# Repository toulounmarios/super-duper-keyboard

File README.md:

helloooooooooooooooooooooo, if you are reading this then you are at the readme section of this repo, so pretty am i right? i know, i know.
im building this project so that i can FINALLY step away from using an old 25 euro gaming keyboard with blue switches ( VERY LOUD ) and make
a compact and aesthetic split keyboad that looks and sounds nice, while also not waking up my entire family at 3am while playing ultrakill or Apex Legends ( both goated btw).
anyways, for anyone who is suprisingly interested in my project here are the key components of the build as well as my key take aways from my first project and some inspo for this.

  first of all, the microcontrollers im using are a pair of seeed xiao nRF52840s, the normal ones will do just fine.
    the pcb was designed on kicad with the libraries from the hackclub stasis event starter project (the split keyboard one) and is manufactured via jlcpcb
   my switches are the kailh choc v2 deep sea silent whale brown switches, due to their tactile yet silent profile.
   for the batteries i havent decided on a li-po battery size for now
  both the case and keycaps ill design after i get the pcb in hand for refernce and ideas 

Now, as for my mistakes, there are afew:

 &emsp; 1) its best to split the work into chunks and finish them consistently. you dont have to do evrything immidiatly, 
    but try to do related tasks back to back to avoid forgetting where you are at in the build process

 &emsp; 2) try to simplify your models in the pcb editor as much as possible. this is because services like jlcpcb change the shipping 
    and manufacturing costs drastically depending on the size of the pcb, but also stuff like the number of layers on your pcb or the pating and stuff

 &emsp; 3) thats it for now

my key inspo for this project was the corne layout for split keyboards and the typeractive corn pcb aluminum case for the pcb and case design

here are the schematics: [schematic](KiCAD_files/keyboard_1.kicad_sch)

here is the pcb design for you to put it into jlcpcb: [pcb](KiCAD_files/keyboard_1.kicad_pcb)

here are pics of the bottom and top plates of the case (all files are in the 3D models folder): 

also here are some sweet renders! 

here is the BOM :

| Name                                           | Purpose                                        | Qty | Total (USD) | Link                                                                                                                                                                                                                                                                                                                                                                                                                                                                                                                                                                                                                                                                                                                                                                                                                                                                                                                                                                                                                                                          | Distributor  |   |
|------------------------------------------------|------------------------------------------------|-----|-------------|---------------------------------------------------------------------------------------------------------------------------------------------------------------------------------------------------------------------------------------------------------------------------------------------------------------------------------------------------------------------------------------------------------------------------------------------------------------------------------------------------------------------------------------------------------------------------------------------------------------------------------------------------------------------------------------------------------------------------------------------------------------------------------------------------------------------------------------------------------------------------------------------------------------------------------------------------------------------------------------------------------------------------------------------------------------|--------------|---|
|                                                |                                                |     |             |                                                                                                                                                                                                                                                                                                                                                                                                                                                                                                                                                                                                                                                                                                                                                                                                                                                                                                                                                                                                                                                               |              |   |
|                                                |                                                |     |             |                                                                                                                                                                                                                                                                                                                                                                                                                                                                                                                                                                                                                                                                                                                                                                                                                                                                                                                                                                                                                                                               |              |   |
| Seeed Studio XIAO nRF52840 (XIAO BLE)          | they are the microcontrollers                  | 2   | $19.80      | <a href=https://www.seeedstudio.com/Seeed-XIAO-BLE-nRF52840-p-5201.html>link</a>                                                                                                                                                                                                                                                                                                                                                                                                                                                                                                                                                                                                                                                                                                                                                                                                                                                                                                                                                                              | seeed studio |   |
|                                                |                                                |     |             |                                                                                                                                                                                                                                                                                                                                                                                                                                                                                                                                                                                                                                                                                                                                                                                                                                                                                                                                                                                                                                                               |              |   |
|                                                |                                                |     |             |                                                                                                                                                                                                                                                                                                                                                                                                                                                                                                                                                                                                                                                                                                                                                                                                                                                                                                                                                                                                                                                               |              |   |
| 0805 806k resistors                            | for part of vbat                               | 100 | $1.68       | <a href=https://www.aliexpress.com/item/1005005184230104.html?spm=a2g0o.productlist.main.1.6249IJXxIJXxPH&algo_pvid=938eadd9-71ba-4352-88da-76219ebfed72&algo_exp_id=938eadd9-71ba-4352-88da-76219ebfed72-0&pdp_ext_f=%7B%22order%22%3A%2216%22%2C%22eval%22%3A%221%22%2C%22fromPage%22%3A%22search%22%7D&pdp_npi=6%40dis%21EUR%212.25%210.86%21%21%2117.66%216.76%21%402103894417762777976955069ec2d7%2112000032017018112%21sea%21GR%216010249690%21ABX%211%210%21n_tag%3A-29910%3Bd%3A8b9bcfc7%3Bm03_new_user%3A-29895%3BpisId%3A5000000203610259&curPageLogUid=4cgpcI0GnRlD&utparam-url=scene%3Asearch%7Cquery_from%3A%7Cx_object_id%3A1005005184230104%7C_p_origin_prod%3A>link</a>                                                                                                                                                                                                                                                                                                                                                                       | aliexpress   |   |
|                                                |                                                |     |             |                                                                                                                                                                                                                                                                                                                                                                                                                                                                                                                                                                                                                                                                                                                                                                                                                                                                                                                                                                                                                                                               |              |   |
|                                                |                                                |     |             |                                                                                                                                                                                                                                                                                                                                                                                                                                                                                                                                                                                                                                                                                                                                                                                                                                                                                                                                                                                                                                                               |              |   |
| 0805 2M resistors                              | for the bt pin                                 | 100 | $2.18       | <a href=https://www.aliexpress.com/item/1005006984056678.html?spm=a2g0o.productlist.main.2.7815aVFfaVFfLN&algo_pvid=960215ef-88d4-41a2-85b6-4be4d2de7d72&algo_exp_id=960215ef-88d4-41a2-85b6-4be4d2de7d72-1&pdp_ext_f=%7B%22order%22%3A%22106%22%2C%22eval%22%3A%221%22%2C%22fromPage%22%3A%22search%22%7D&pdp_npi=6%40dis%21EUR%211.76%210.86%21%21%2113.79%216.72%21%402103963717762779223528530e0524%2112000038943042424%21sea%21GR%216010249690%21ABX%211%210%21n_tag%3A-29910%3Bd%3A8b9bcfc7%3Bm03_new_user%3A-29895%3BpisId%3A5000000203610259&curPageLogUid=NDv0RorZTDqo&utparam-url=scene%3Asearch%7Cquery_from%3A%7Cx_object_id%3A1005006984056678%7C_p_origin_prod%3A>link</a>                                                                                                                                                                                                                                                                                                                                                                      | aliexpress   |   |
|                                                |                                                |     |             |                                                                                                                                                                                                                                                                                                                                                                                                                                                                                                                                                                                                                                                                                                                                                                                                                                                                                                                                                                                                                                                               |              |   |
|                                                |                                                |     |             |                                                                                                                                                                                                                                                                                                                                                                                                                                                                                                                                                                                                                                                                                                                                                                                                                                                                                                                                                                                                                                                               |              |   |
| 1N4148W T4 SOD-123 diodes                      | needed for the keyboard matrix                 | 100 | $1.84       | <a href=https://www.aliexpress.com/item/1005010653199938.html?spm=a2g0o.detail.pcDetailTopMoreOtherSeller.9.6064rMHVrMHVt1&gps-id=pcDetailTopMoreOtherSeller&scm=1007.40050.354490.0&scm_id=1007.40050.354490.0&scm-url=1007.40050.354490.0&pvid=9ca8f257-295a-4de2-a5ff-3a8f67253366&_t=gps-id:pcDetailTopMoreOtherSeller,scm-url:1007.40050.354490.0,pvid:9ca8f257-295a-4de2-a5ff-3a8f67253366,tpp_buckets:668%232846%238107%231934&pdp_ext_f=%7B%22order%22%3A%221531%22%2C%22eval%22%3A%221%22%2C%22orig_sl_item_id%22%3A%221005010653199938%22%2C%22orig_item_id%22%3A%221005007160563285%22%2C%22sceneId%22%3A%2230050%22%2C%22fromPage%22%3A%22recommend%22%7D&pdp_npi=6%40dis%21EUR%211.34%210.86%21%21%2110.50%216.70%21%40211b612517762807244226998ec4d3%2112000053087454998%21rec%21GR%216010249690%21ABXZ%211%210%21n_tag%3A-29910%3Bd%3A8b9bcfc7%3Bm03_new_user%3A-29895%3BpisId%3A5000000203610259&utparam-url=scene%3ApcDetailTopMoreOtherSeller%7Cquery_from%3A%7Cx_object_id%3A1005010653199938%7C_p_origin_prod%3A1005007160563285>link</a> | aliexpress   |   |
|                                                |                                                |     |             |                                                                                                                                                                                                                                                                                                                                                                                                                                                                                                                                                                                                                                                                                                                                                                                                                                                                                                                                                                                                                                                               |              |   |
|                                                |                                                |     |             |                                                                                                                                                                                                                                                                                                                                                                                                                                                                                                                                                                                                                                                                                                                                                                                                                                                                                                                                                                                                                                                               |              |   |
| kailh choc v2 hotswap sockets                  | the are the hotswap sockets for my keyswitches | 50  | $5.81       | <a href=https://www.aliexpress.com/item/1005006610506123.html?pdp_npi=4%40dis%21EUR%213.60%211.51%21%21%2129.54%2112.37%21%402141329e17534982253082340d184a%2112000037826084041%21affd%21%21%21&cv=c45834a1-6097-4ce5-bd0a-eecf81d5bb63&gclid=Cj0KCQjwy_fOBhC6ARIsAHKFB79GB903IfZviU8ujcMX8Y--gl5Zxm7TP2JwkSXSLCZnXrenfdEWX5QaAnXwEALw_wcB&aff_fcid=73996a7b7e504db59aeb61aecc68347f-1776206585399-09693&aff_fsk&aff_platform=api-new-product-query&sk&aff_trace_key=73996a7b7e504db59aeb61aecc68347f-1776206585399-09693&terminal_id=88e593aa98a443b1bd172a14f593b1ca&afSmartRedirect=y>link</a>                                                                                                                                                                                                                                                                                                                                                                                                                                                             | aliexpress   |   |
|                                                |                                                |     |             |                                                                                                                                                                                                                                                                                                                                                                                                                                                                                                                                                                                                                                                                                                                                                                                                                                                                                                                                                                                                                                                               |              |   |
|                                                |                                                |     |             |                                                                                                                                                                                                                                                                                                                                                                                                                                                                                                                                                                                                                                                                                                                                                                                                                                                                                                                                                                                                                                                               |              |   |
| kailh choc v2 deep sea silent mini whale brown | they are the keyswitches                       | 50  | $12.97      | <a href=https://www.aliexpress.com/item/1005008382793794.html?spm=a2g0o.cart.0.0.695838daIfg5m9&mp=1&pdp_npi=6%40dis%21EUR%21EUR%2032.40%21EUR%2010.99%21%21EUR%2010.99%21%21%21%40211b629217762869039837251e1abb%2112000044795077989%21ct%21GR%216010249690%21%211%210%21>link</a>                                                                                                                                                                                                                                                                                                                                                                                                                                                                                                                                                                                                                                                                                                                                                                           | aliexpress   |   |
|                                                |                                                |     |             |                                                                                                                                                                                                                                                                                                                                                                                                                                                                                                                                                                                                                                                                                                                                                                                                                                                                                                                                                                                                                                                               |              |   |
|                                                |                                                |     |             |                                                                                                                                                                                                                                                                                                                                                                                                                                                                                                                                                                                                                                                                                                                                                                                                                                                                                                                                                                                                                                                               |              |   |
| the pcb                                        | its the pcb                                    | 5   | $15.80      | (jlcpcb wont let me share my cart so youll have to do it yourself via jlcpcb)                                                                                                                                                                                                                                                                                                                                                                                                                                                                                                                                                                                                                                                                                                                                                                                                                                                                                                                                                                                 | jlcpcb       |   |
|                                                |                                                |     |             |                                                                                                                                                                                                                                                                                                                                                                                                                                                                                                                                                                                                                                                                                                                                                                                                                                                                                                                                                                                                                                                               |              |   |
|                                                |                                                |     |             |                                                                                                                                                                                                                                                                                                                                                                                                                                                                                                                                                                                                                                                                                                                                                                                                                                                                                                                                                                                                                                                               |              |   |
| 3.7v li-po 501350 batteries                    | they are the batteries for the keyboard        | 2   | $11.08      | <a href=https://www.aliexpress.com/item/1005011541459046.html?spm=a2g0o.productlist.main.11.4ed12433TM4x7g&algo_pvid=8316d1d1-ff45-4c59-8bb0-ead331b8cc5e&algo_exp_id=8316d1d1-ff45-4c59-8bb0-ead331b8cc5e-10&pdp_ext_f=%7Border%3A6%2Ceval%3A1%2CfromPage%3Asearch%7D&pdp_npi=6%40dis%21EUR%219.45%219.45%21%21%2173.72%2173.71%21%40211b80c217770748274287120e82a1%2112000055867197802%21sea%21GR%216010249690%21ABX%211%210%21n_tag%3A-29910%3Bd%3A8b9bcfc7%3Bm03_new_user%3A-29895&curPageLogUid=aRGigff6t9rL&utparam-url=scene%3Asearch%7Cquery_from%3A%7Cx_object_id%3A1005011541459046%7C_p_origin_prod%3A>link</a>                                                                                                                                                                                                                                                                                                                                                                                                                                    | aliexpress   |   |
|                                                |                                                |     |             |                                                                                                                                                                                                                                                                                                                                                                                                                                                                                                                                                                                                                                                                                                                                                                                                                                                                                                                                                                                                                                                               |              |   |
|                                                |                                                |     |             |                                                                                                                                                                                                                                                                                                                                                                                                                                                                                                                                                                                                                                                                                                                                                                                                                                                                                                                                                                                                                                                               |              |   |
| 8mm m3 screw standoffs                         | they are the standoffs for the case            | 30  | $4.05       | <a href=https://www.aliexpress.com/item/1005002952338852.html?spm=a2g0o.productlist.main.2.76a7fdqufdquHE&algo_pvid=8a34bb07-f5e5-4cf5-919e-072324ce4bfc&algo_exp_id=8a34bb07-f5e5-4cf5-919e-072324ce4bfc-1&pdp_ext_f=%7Border%3A4531%2Ceval%3A1%2CfromPage%3Asearch%7D&pdp_npi=6%40dis%21EUR%213.45%210.86%21%21%2127.01%216.77%21%40211b6c1717778417414317970e04bb%2112000022953911085%21sea%21GR%216010249690%21ABX%211%210%21n_tag%3A-29910%3Bd%3A8b9bcfc7%3Bm03_new_user%3A-29895%3BpisId%3A5000000203887847&curPageLogUid=u8OJuwyjTbWf&utparam-url=scene%3Asearch%7Cquery_from%3A%7Cx_object_id%3A1005002952338852%7C_p_origin_prod%3A>link</a>                                                                                                                                                                                                                                                                                                                                                                                                         | aliexpress   |   |
|                                                |                                                |     |             |                                                                                                                                                                                                                                                                                                                                                                                                                                                                                                                                                                                                                                                                                                                                                                                                                                                                                                                                                                                                                                                               |              |   |
|                                                |                                                |     |             |                                                                                                                                                                                                                                                                                                                                                                                                                                                                                                                                                                                                                                                                                                                                                                                                                                                                                                                                                                                                                                                               |              |   |
| 8mm m3 screws                                  | they are the screws for the build              | 50  | $2.89       | <a href=https://www.aliexpress.com/item/1005005618746295.html?spm=a2g0o.productlist.main.12.47bdiGGViGGVl8&aem_p4p_detail=2026050314395414124994392997550004262633&algo_pvid=af90b46d-2b12-4a03-9fbb-445107ef9b00&algo_exp_id=af90b46d-2b12-4a03-9fbb-445107ef9b00-11&pdp_ext_f=%7Border%3A7662%2Ceval%3A1%2CfromPage%3Asearch%7D&pdp_npi=6%40dis%21EUR%211.34%210.86%21%21%2110.45%216.76%21%402103867617778443947378432ef33c%2112000033767212213%21sea%21GR%216010249690%21ABX%211%210%21n_tag%3A-29910%3Bd%3A8b9bcfc7%3Bm03_new_user%3A-29895%3BpisId%3A5000000203887870&curPageLogUid=aeUfHf83b7Vf&utparam-url=scene%3Asearch%7Cquery_from%3A%7Cx_object_id%3A1005005618746295%7C_p_origin_prod%3A&search_p4p_id=2026050314395414124994392997550004262633_3>link</a>                                                                                                                                                                                                                                                                                      | aliexpress   |   |

  important notes for ordering and assembly: 

&emsp;1) the resistors for some reason when pressing the link have a different option selected and you'll have to change it yourself in reference to the BOM
&emsp;2) jlcpcb doesnt let you share a link with your cart, so you'll have to go into the jlcpcb site and import the pcb file and then select the options you want, as well as the color of the pcb.
&emsp;3) in the BOM, im not including filament as part of the cost to make the case and the keycaps, because the price changes drastically depending on what filament you use and so it wouldnt really make sense to add
        it as it would be inaccurate. as a rough estimate tho, with around 250-300 gr of pla filament ( around 6-10$ ), you should be set

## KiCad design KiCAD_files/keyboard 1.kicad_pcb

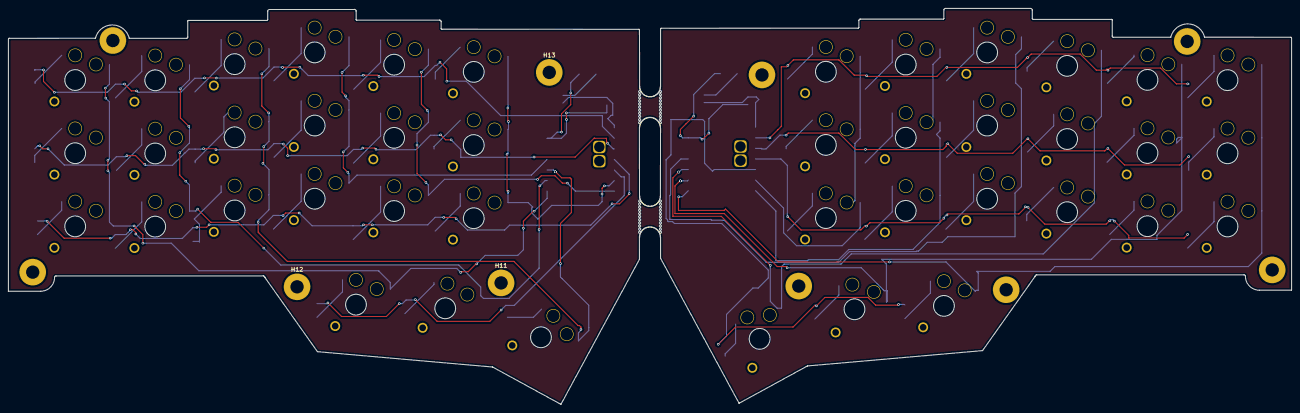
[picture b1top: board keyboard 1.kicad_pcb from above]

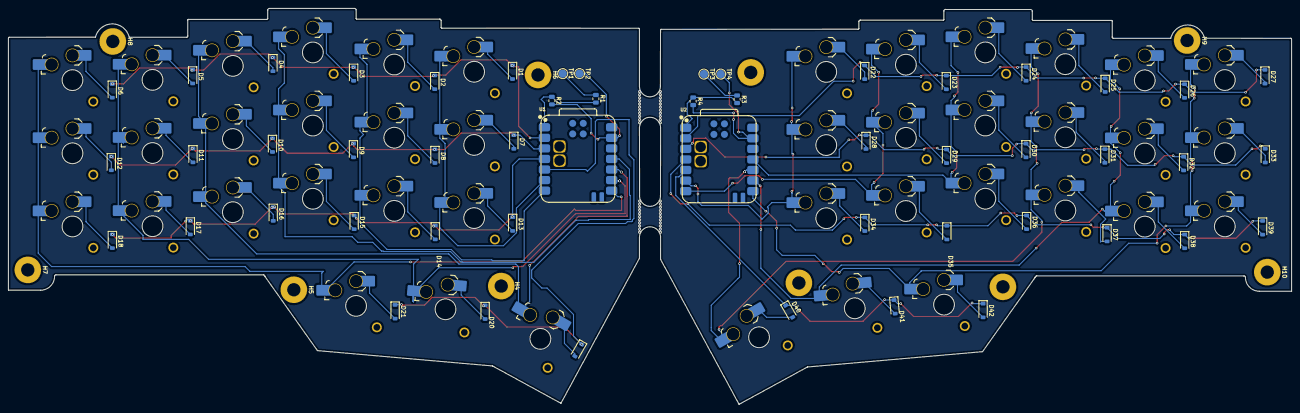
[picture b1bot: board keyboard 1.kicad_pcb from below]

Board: 2 copper layers, 308.6 x 95.2 mm, 106 parts (101 on the bottom side), 67 nets.

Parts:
D1, D2, D3, D4, D5, D6, D7, D8, D9, D10, D11, D12, D13, D14, D15, D16, D17, D18, D19, D20, D21, D22, D23, D24, D25, D26, D27, D28, D29, D30, D31, D32, D33, D34, D35, D36, D37, D38, D39, D40, D41, D42: D; D_SOD-123
H2, H3: MountingHole; mouse-bite-5mm-slot
H4, H5, H6, H7, H8, H9, H10, H11, H12, H13: MountingHole; MountingHole_3.2mm_M3_Pad
R1, R3: 806k; R_0805_2012Metric
R2, R4: 2M; R_0805_2012Metric
SW1, SW2, SW3, SW4, SW5, SW6, SW7, SW8, SW9, SW10, SW11, SW12, SW13, SW14, SW15, SW16, SW17, SW18, SW19, SW20, SW21, SW22, SW23, SW24, SW25, SW26, SW27, SW28, SW29, SW30, SW31, SW32, SW33, SW34, SW35, SW36, SW37, SW38, SW39, SW40, SW41, SW42: SW_Push; SW_choc_v2_HS_CPG135001S30_1u
TP1, TP2, TP3, TP4: TestPoint; TestPoint_Pad_D2.0mm
U1, U2: XIAO-nRF52840-SMD; modified-XIAO-nRF52840-SMD

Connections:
/left/BT_PIN: R1.2, R2.1, U1.1 (P0.02_A0_D0)
/left/VBAT: R1.1, TP1.1
/left/col1: SW1.1, SW7.1, SW13.1, U1.6 (P0.05_A5_D5_SCL)
/left/col2: SW2.1, SW8.1, SW14.1, U1.7 (P1.11_D6_TX)
/left/col3: SW3.1, SW9.1, SW15.1, U1.11 (P1.15_D10_MOSI)
/left/col4: SW4.1, SW10.1, SW16.1, SW19.1, U1.10 (P1.14_D9_MISO)
/left/col5: SW5.1, SW11.1, SW17.1, SW20.1, U1.9 (P1.13_D8_SCK)
/left/col6: SW6.1, SW12.1, SW18.1, SW21.1, U1.8 (P1.12_D7_RX)
/left/row 1: D1.1 (K), D2.1 (K), D3.1 (K), D4.1 (K), D5.1 (K), D6.1 (K), U1.2 (P0.03_A1_D1)
/left/row 2: D7.1 (K), D8.1 (K), D9.1 (K), D10.1 (K), D11.1 (K), D12.1 (K), U1.3 (P0.28_A2_D2)
/left/row 3: D13.1 (K), D14.1 (K), D15.1 (K), D16.1 (K), D17.1 (K), D18.1 (K), U1.4 (P0.29_A3_D3)
/left/row 4: D19.1 (K), D20.1 (K), D21.1 (K), U1.5 (P0.04_A4_D4_SDA)
/right/BT_PIN: R3.2, R4.1, U2.1 (P0.02_A0_D0)
/right/VBAT: R3.1, TP3.1
/right/col1: SW22.1, SW28.1, SW34.1, U2.6 (P0.05_A5_D5_SCL)
/right/col2: SW23.1, SW29.1, SW35.1, U2.7 (P1.11_D6_TX)
/right/col3: SW24.1, SW30.1, SW36.1, U2.11 (P1.15_D10_MOSI)
/right/col4: SW25.1, SW31.1, SW37.1, SW40.1, U2.10 (P1.14_D9_MISO)
/right/col5: SW26.1, SW32.1, SW38.1, SW41.1, U2.9 (P1.13_D8_SCK)
/right/col6: SW27.1, SW33.1, SW39.1, SW42.1, U2.8 (P1.12_D7_RX)
/right/row 1: D22.1 (K), D23.1 (K), D24.1 (K), D25.1 (K), D26.1 (K), D27.1 (K), U2.2 (P0.03_A1_D1)
/right/row 2: D28.1 (K), D29.1 (K), D30.1 (K), D31.1 (K), D32.1 (K), D33.1 (K), U2.3 (P0.28_A2_D2)
/right/row 3: D34.1 (K), D35.1 (K), D36.1 (K), D37.1 (K), D38.1 (K), D39.1 (K), U2.4 (P0.29_A3_D3)
/right/row 4: D40.1 (K), D41.1 (K), D42.1 (K), U2.5 (P0.04_A4_D4_SDA)
GND: R2.2, R4.2, TP2.1, TP4.1, U1.13 (GND), U2.13 (GND)
unnamed: D1.2 (A), SW1.2
unnamed: D2.2 (A), SW2.2
unnamed: D3.2 (A), SW3.2
unnamed: D4.2 (A), SW4.2
unnamed: D5.2 (A), SW5.2
unnamed: D6.2 (A), SW6.2
unnamed: D7.2 (A), SW7.2
unnamed: D8.2 (A), SW8.2
unnamed: D9.2 (A), SW9.2
unnamed: D10.2 (A), SW10.2
unnamed: D11.2 (A), SW11.2
unnamed: D12.2 (A), SW12.2
unnamed: D13.2 (A), SW13.2
unnamed: D14.2 (A), SW14.2
unnamed: D15.2 (A), SW15.2
unnamed: D16.2 (A), SW16.2
unnamed: D17.2 (A), SW17.2
unnamed: D18.2 (A), SW18.2
unnamed: D19.2 (A), SW19.2
unnamed: D20.2 (A), SW20.2
unnamed: D21.2 (A), SW21.2
unnamed: D22.2 (A), SW22.2
unnamed: D23.2 (A), SW23.2
unnamed: D24.2 (A), SW24.2
unnamed: D25.2 (A), SW25.2
unnamed: D26.2 (A), SW26.2
unnamed: D27.2 (A), SW27.2
unnamed: D28.2 (A), SW28.2
unnamed: D29.2 (A), SW29.2
unnamed: D30.2 (A), SW30.2
unnamed: D31.2 (A), SW31.2
unnamed: D32.2 (A), SW32.2
unnamed: D33.2 (A), SW33.2
unnamed: D34.2 (A), SW34.2
unnamed: D35.2 (A), SW35.2
unnamed: D36.2 (A), SW36.2
unnamed: D37.2 (A), SW37.2
unnamed: D38.2 (A), SW38.2
unnamed: D39.2 (A), SW39.2
unnamed: D40.2 (A), SW40.2
unnamed: D41.2 (A), SW41.2
unnamed: D42.2 (A), SW42.2

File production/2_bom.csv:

Designator,Footprint,Quantity,Value,LCSC Part #
"D1, D10, D11, D12, D13, D14, D15, D16, D17, D18, D19, D2, D20, D21, D22, D23, D24, D25, D26, D27, D28, D29, D3, D30, D31, D32, D33, D34, D35, D36, D37, D38, D39, D4, D40, D41, D42, D5, D6, D7, D8, D9",D_SOD-123,42,D,
"R1, R3",0805,2,806k,
"R2, R4",0805,2,2M,
"SW1, SW10, SW11, SW12, SW13, SW14, SW15, SW16, SW17, SW18, SW19, SW2, SW20, SW21, SW22, SW23, SW24, SW25, SW26, SW27, SW28, SW29, SW3, SW30, SW31, SW32, SW33, SW34, SW35, SW36, SW37, SW38, SW39, SW4, SW40, SW41, SW42, SW5, SW6, SW7, SW8, SW9",SW_choc_v2_HS_CPG135001S30_1u,42,SW_Push,
"TP1, TP2, TP3, TP4",TestPoint_Pad_D2.0mm,4,TestPoint,
"U1, U2",modified-XIAO-nRF52840-SMD,2,XIAO-nRF52840-SMD,

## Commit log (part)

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2026-04-16 Create README.md with project details and insights
    Added project overview, components, mistakes, and inspirations.
2026-04-16 Add image and refine README content
    Added an image to the README and improved text clarity.
2026-04-16 Update README to include STEP file information
    Added STEP file reference to the README.
2026-04-24 Create kicad files
2026-04-24 Create h
2026-04-24 Update README with STEP file and BOM details
    Added information about the STEP file and BOM for the project.
2026-04-24 Fix link for Seeed Studio XIAO nRF52840 in README
    Updated the link for Seeed Studio XIAO nRF52840 in the BOM.
2026-04-24 Update README with BOM for custom case components
    Added Bill of Materials (BOM) with components and links.
2026-04-24 Update link for Seeed Studio XIAO nRF52840
2026-04-24 Correct BOM formatting in README.md
    Fix formatting issues in BOM section of README.
2026-04-24 Correct BOM formatting in README.md
    Fix formatting issues in the BOM section of README.
2026-04-24 Clarify PCB link description in README
    Updated the PCB link description for clarity.
2026-04-24 Update PCB description in README.md
    Fixed formatting and improved readability of PCB description.
2026-04-24 Fix typos and enhance README content
    Corrected typos and improved readability in the README.
2026-04-24 Fix formatting and typos in README.md
    Corrected formatting and spelling errors in the README.
2026-04-24 Revise README with project overview and BOM
    Updated the README to include project details and components.
2026-04-24 Improve formatting and readability of README.md
    Formatted the README content for better readability and consistency.
2026-04-24 Update README with project details and insights
    Refined the README to improve clarity and fix typos.
2026-04-24 Fix formatting and typos in README.md
    Removed HTML entities and corrected typos in the README.
2026-04-24 Add ordering and assembly notes to README
    Added important notes regarding ordering and assembly instructions for the PCB.
2026-04-24 Update README with link to PCB step file
2026-04-24 Fix link to PCB step file in README
2026-04-24 Fix link path for PCB step file in README
2026-04-24 Fix link format for PCB step file in README
2026-04-24 Update link to PCB step file location
2026-04-24 Fix link formatting for PCB step file in README
2026-04-24 Rename keyboard 1.step to keyboard_1.step
2026-04-24 Fix schematics link for PCB in README
    Updated the link for the PCB schematics in the README.
2026-04-24 Clarify schematic link and add PCB design reference
    Updated links in README for clarity and added PCB design reference.
2026-04-24 Update README to clarify PCB model reference
2026-04-24 Update PCB design link in README
2026-04-24 Enhance README with image and PCB model link
    Added an image and a link to the PCB 3D model in the README.
2026-04-24 Update README with clearer project inspiration details
    Clarified the description of project inspiration.
2026-04-24 Revise battery details and assembly notes in README
    Updated battery information and added important notes for ordering and assembly.
2026-04-25 Update filament cost explanation in README
    Clarified the explanation regarding filament costs in the BOM.
2026-04-25 Remove LCSC Part # column from 3_bom.csv
    Removed LCSC Part # column from BOM file.
2026-04-25 Update 3_bom.csv to include links section
    Added links section to the BOM file.
2026-05-03 Add battery and standoff details to README
2026-05-03 Fix formatting for standoffs entry in README
2026-05-03 Include case plate images in README
    Added images of the bottom and top plates of the case.
2026-05-10 Revise BOM table formatting in README
    Updated the BOM table format for better readability.
2026-05-10 Create g
2026-06-03 Create :3
2026-06-03 Update README with inline images and remove step file
    Removed the step file link and updated render image links to inline images.
2026-06-12 Rename all_pics/1780520341832-jf8900.webp to finalpcb.webp
2026-06-12 Change PCB image to finalpcb.webp
    Updated PCB image format from PNG to WEBP.
2026-06-12 Rename finalpcb.webp to all_pics/finalpcb.webp
2026-06-17 Create gerber and drill files
2026-06-17 Create k
